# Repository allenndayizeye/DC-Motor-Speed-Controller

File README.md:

# DC-Motor-Speed-Controller

This project is a closed-loop PI speed controller for a DC motor. It uses an MSP430 microcontroller to generate PWM signals and a custom-designed H-Bridge PCB to drive the motor. Varying loads were added to a second generator motor for different current draws and to monitor the PI controllers response.

### Project Showcase

### Key Features
* **Control:** A software PI controller implemented in C precisely regulates motor speed to a desired setpoint that is input by the user.
* **Hardware:** A custom PCB for the H-Bridge power driver was designed in KiCad to handle high motor currents.
* **Feedback System:** Uses a Hall effect encoder to process real-time speed feedback.
* **Performance:** The system was tuned to achieve a settling time of 3 seconds with minimal overshoot (less than 50 RPM).

### Technologies Used
* **Microcontroller:** TI MSP430
* **PCB Design:** KiCad
* **Hardware:** Custom H-Bridge with MOSFETs, Hall Effect Encoder

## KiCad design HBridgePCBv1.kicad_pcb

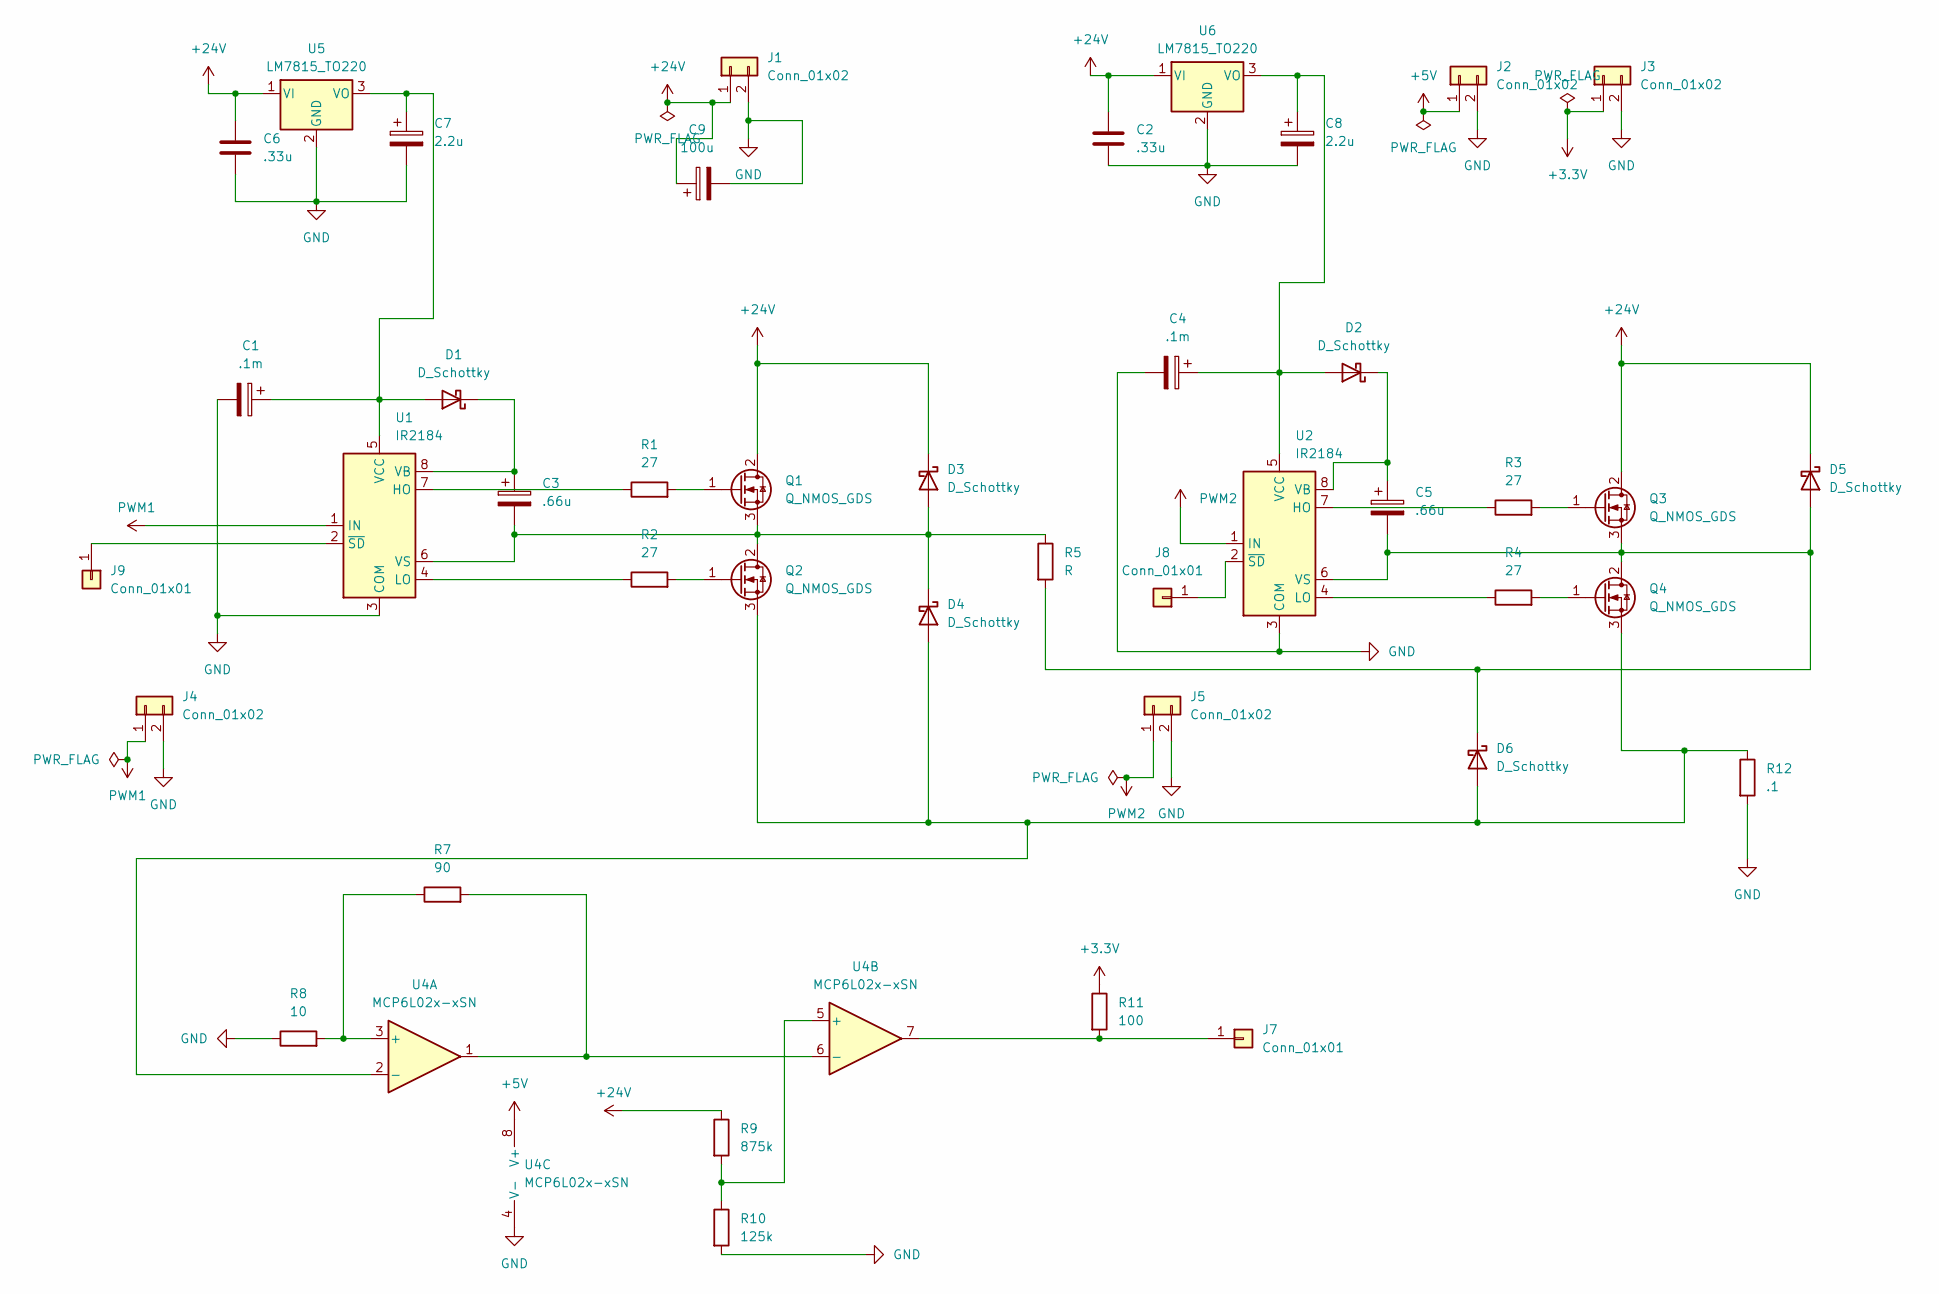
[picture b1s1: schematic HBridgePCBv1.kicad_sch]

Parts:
C1, C4: .1m; CP_Radial_D10.0mm_P5.00mm
C2, C6: .33u; C_Disc_D7.5mm_W5.0mm_P5.00mm
C3, C5: .66u; CP_Radial_D10.0mm_P5.00mm
C7, C8: 2.2u; CP_Radial_D10.0mm_P5.00mm
C9: 100u; CP_Radial_D10.0mm_P5.00mm
D1, D2, D3, D4, D5, D6: D_Schottky; D_DO-35_SOD27_P10.16mm_Horizontal
J1: Conn_01x02; TerminalBlock_TE_282834-2_1x02_P2.54mm_Horizontal
J2, J3, J4, J5: Conn_01x02; PinHeader_1x02_P2.54mm_Vertical
J7, J8, J9: Conn_01x01; PinHeader_1x01_P2.54mm_Vertical
Q1, Q2, Q3, Q4: Q_NMOS_GDS; TO-220-3_Vertical
R1, R2, R3, R4: 27; R_Axial_DIN0309_L9.0mm_D3.2mm_P15.24mm_Horizontal
R5: R
R7: 90; R_Axial_DIN0309_L9.0mm_D3.2mm_P15.24mm_Horizontal
R8: 10; R_Axial_DIN0309_L9.0mm_D3.2mm_P15.24mm_Horizontal
R9: 875k; R_Axial_DIN0309_L9.0mm_D3.2mm_P15.24mm_Horizontal
R10: 125k; R_Axial_DIN0309_L9.0mm_D3.2mm_P15.24mm_Horizontal
R11: 100; R_Axial_DIN0309_L9.0mm_D3.2mm_P15.24mm_Horizontal
R12: .1; R_Axial_DIN0309_L9.0mm_D3.2mm_P15.24mm_Horizontal
U1, U2: IR2184; DIP-8_W7.62mm_LongPads
U4: MCP6L02x-xSN; DIP-8_W7.62mm_LongPads
U5, U6: LM7815_TO220; TO-220-3_Vertical

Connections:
+3.3V: J3.1, R11.1
+5V: J2.1, U4.8 (V+)
+24V: C2.1, C6.1, C9.1, D3.1 (K), D5.1 (K), J1.1, Q1.2 (D), Q3.2 (D), R9.1, U5.1 (VI), U6.1 (VI)
GND: C1.2, C2.2, C4.2, C6.2, C7.2, C8.2, C9.2, J1.2, J2.2, J3.2, J4.2, J5.2, R8.1, R10.2, R12.2, U1.3 (COM), U2.3 (COM), U4.4 (V-), U5.2 (GND), U6.2 (GND)
unnamed: C1.1, C7.1, D1.2 (A), U1.5 (VCC), U5.3 (VO)
unnamed: C3.1, D1.1 (K), U1.8 (VB)
unnamed: C4.1, C8.1, D2.2 (A), U2.5 (VCC), U6.3 (VO)
unnamed: C5.1, D2.1 (K), U2.8 (VB)
unnamed 8: C3.2, D3.2 (A), D4.1 (K), Q1.3 (S), Q2.2 (D), R5.1, U1.6 (VS); also elsewhere on the board
unnamed: D4.2 (A), D6.2 (A), Q2.3 (S), Q4.3 (S), R12.1, U4.2 (-)
unnamed: J7.1, R11.2, U4.7
unnamed: J8.1, U2.2 (~SD)
unnamed: J9.1, U1.2 (~SD)
unnamed: Q1.1 (G), R1.2
unnamed: Q2.1 (G), R2.2
unnamed: Q3.1 (G), R3.2
unnamed: Q4.1 (G), R4.2
unnamed: R1.1, U1.7 (HO)
unnamed: R2.1, U1.4 (LO)
unnamed: R3.1, U2.7 (HO)
unnamed: R4.1, U2.4 (LO)
unnamed: R7.1, R8.2, U4.3 (+)
unnamed: R9.2, R10.1, U4.5 (+)
unnamed: R7.2, U4.1, U4.6 (-)
PWM1: J4.1, U1.1 (IN)
PWM2: J5.1, U2.1 (IN)

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
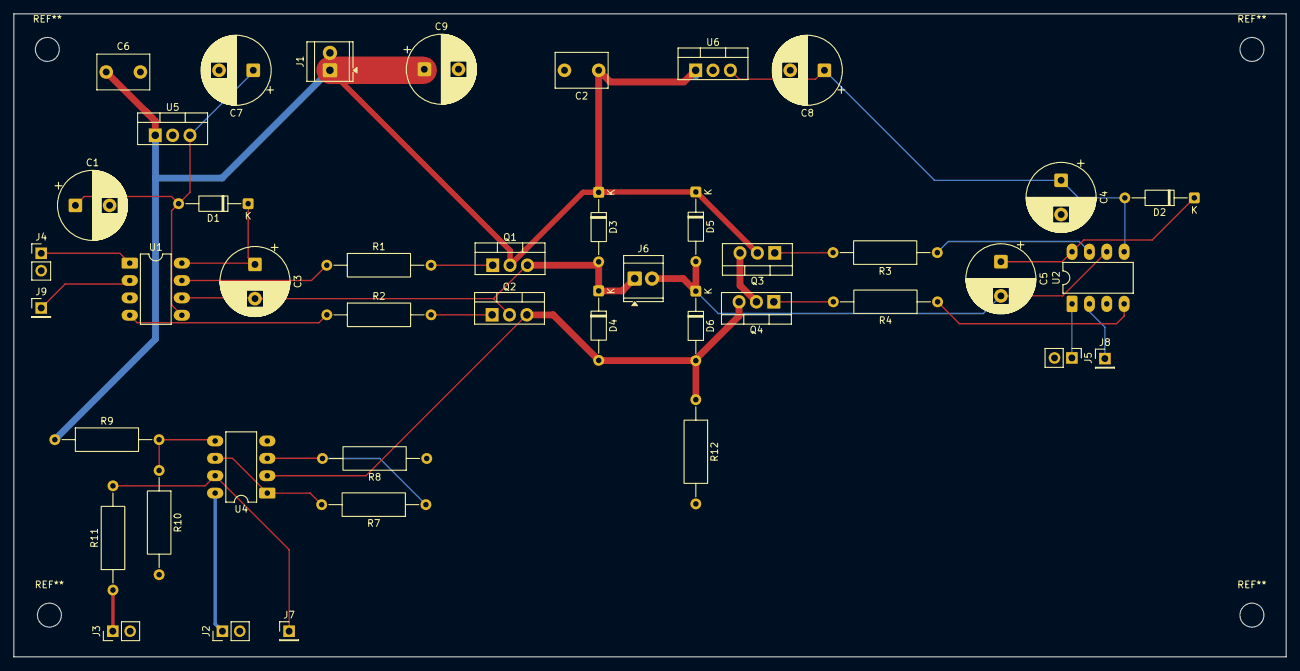
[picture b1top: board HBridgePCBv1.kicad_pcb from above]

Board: 4 copper layers, 186.0 x 94.0 mm, 43 parts (0 on the bottom side), 28 nets.

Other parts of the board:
J6: Conn_01x02; TerminalBlock_TE_282834-2_1x02_P2.54mm_Horizontal

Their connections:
unnamed 8: J6.1; also elsewhere on the board

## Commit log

2025-09-16 Add project photos to images folder
2025-09-16 Rename setup photo
